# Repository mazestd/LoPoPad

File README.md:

# #️⃣ LoPoPad
4x3 Low Profile MacroPad with 1.9" LCD Display

# 💡Intro

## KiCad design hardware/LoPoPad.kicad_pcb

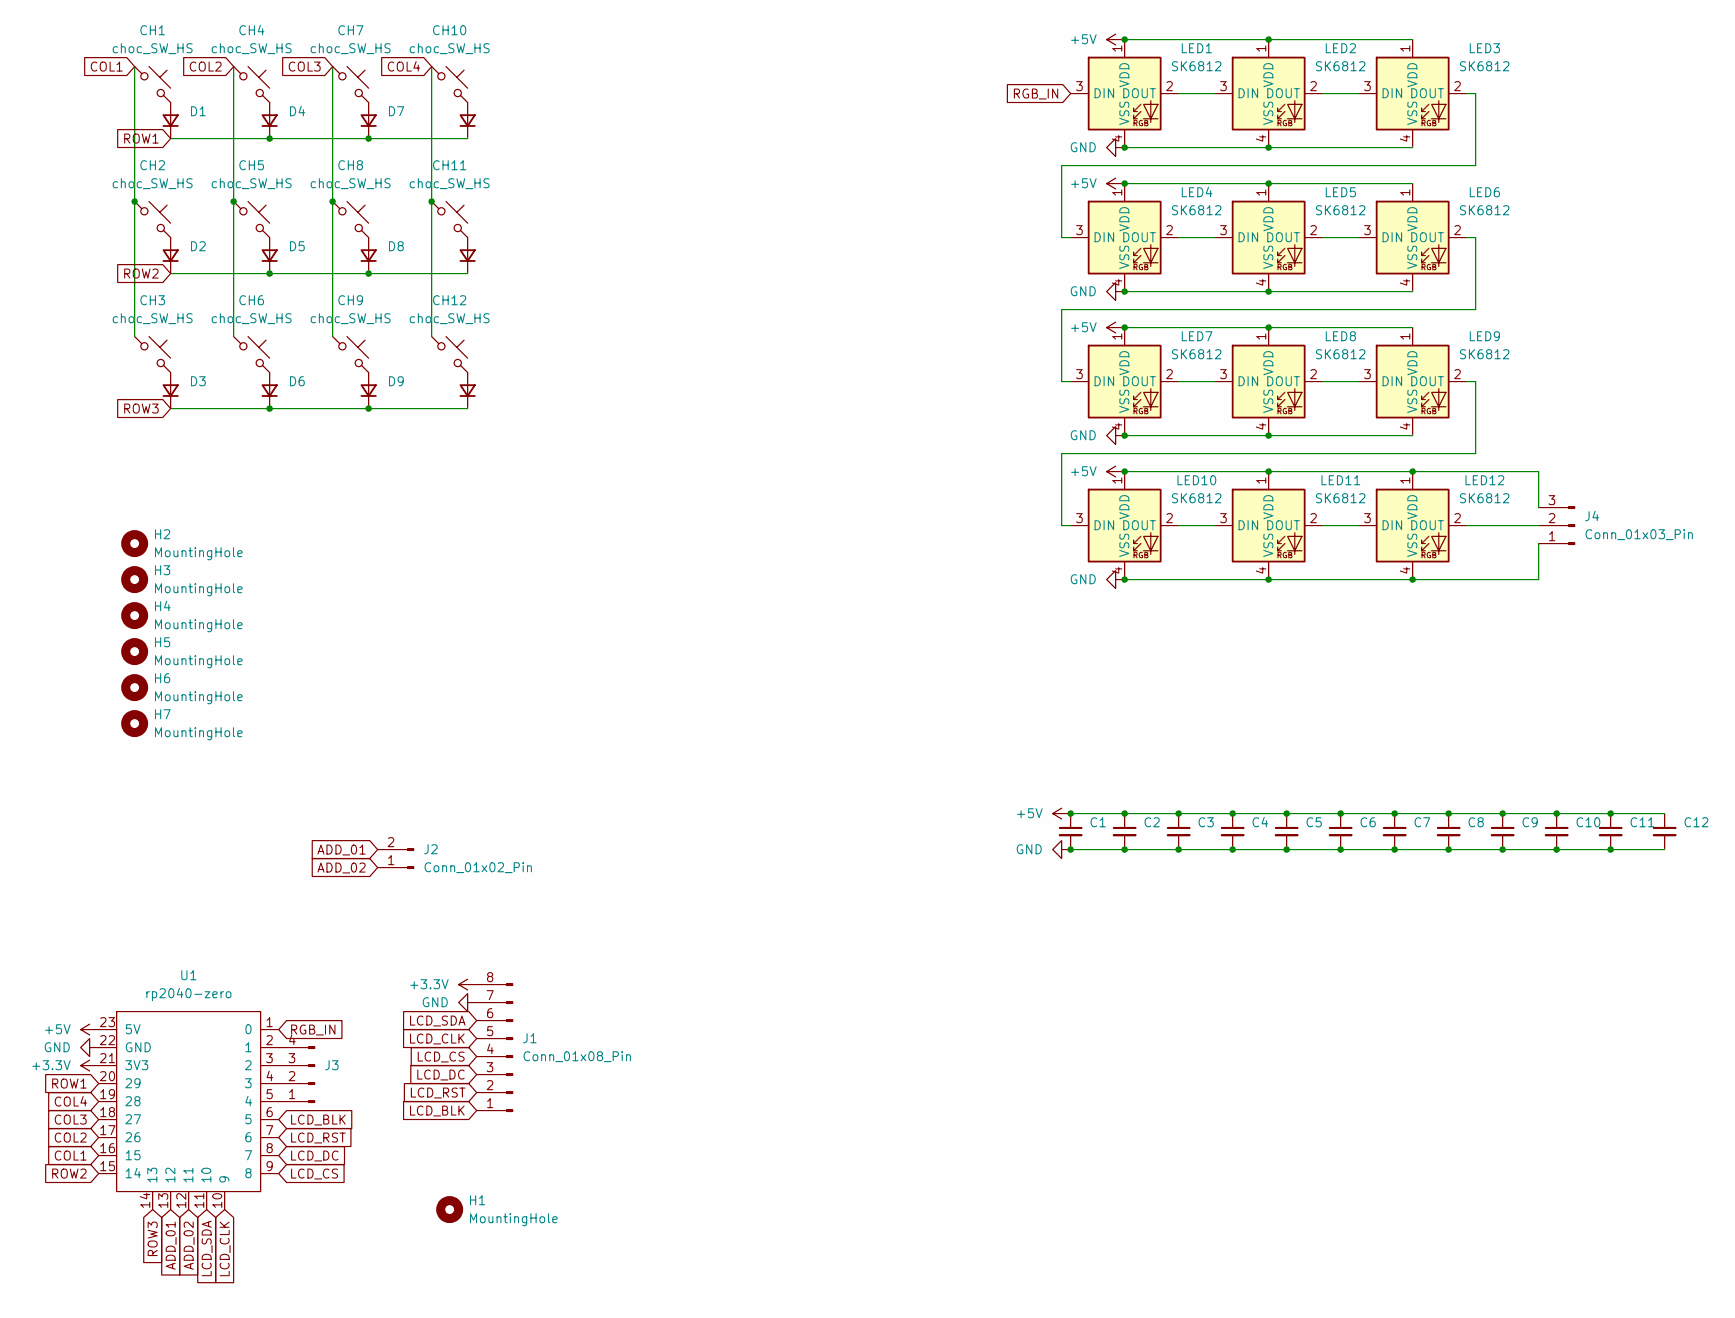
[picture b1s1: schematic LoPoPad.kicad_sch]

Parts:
C1, C2, C3, C4, C5, C6, C7, C8, C9, C10, C11, C12: 100nf; C_0603_1608Metric
CH1, CH2, CH3, CH4, CH5, CH6, CH7, CH8, CH9, CH10, CH11, CH12: choc_SW_HS; SW_choc_v1_HS_1u
D1, D2, D3, D4, D5, D6, D7, D8, D9, D10, D11, D12: 1n4148w; D_SOD-123
H1: MountingHole; soyu_display
H2, H3, H4, H5, H6, H7: MountingHole; MountingHole_2.2mm_M2_ISO14580
J1: Conn_01x08_Pin; Molex_PicoBlade_53261-0871_1x08-1MP_P1.25mm_Horizontal
J2: Conn_01x02_Pin; PinHeader_1x02_P2.54mm_Vertical
J3: Conn_01x04_Pin; PinHeader_1x04_P2.54mm_Vertical
J4: Conn_01x03_Pin; PinHeader_1x03_P2.00mm_Vertical
LED1, LED2, LED3, LED4, LED5, LED6, LED7, LED8, LED9, LED10, LED11, LED12: SK6812; LED_choc_6028R
U1: rp2040-zero; rp2040-zero-smd

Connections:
+3.3V: J1.8, U1.21 (3V3)
+5V: C1.1, C2.1, C3.1, C4.1, C5.1, C6.1, C7.1, C8.1, C9.1, C10.1, C11.1, C12.1, J4.3, LED1.1 (VDD), LED2.1 (VDD), LED3.1 (VDD), LED4.1 (VDD), LED5.1 (VDD), LED6.1 (VDD), LED7.1 (VDD), LED8.1 (VDD), LED9.1 (VDD), LED10.1 (VDD), LED11.1 (VDD), LED12.1 (VDD), U1.23 (5V)
ADD_01: J2.2, U1.13 (12)
ADD_02: J2.1, U1.12 (11)
COL1: CH1.1, CH2.1, CH3.1, U1.16 (15)
COL2: CH4.1, CH5.1, CH6.1, U1.17 (26)
COL3: CH7.1, CH8.1, CH9.1, U1.18 (27)
COL4: CH10.1, CH11.1, CH12.1, U1.19 (28)
GND: C1.2, C2.2, C3.2, C4.2, C5.2, C6.2, C7.2, C8.2, C9.2, C10.2, C11.2, C12.2, J1.7, J4.1, LED1.4 (VSS), LED2.4 (VSS), LED3.4 (VSS), LED4.4 (VSS), LED5.4 (VSS), LED6.4 (VSS), LED7.4 (VSS), LED8.4 (VSS), LED9.4 (VSS), LED10.4 (VSS), LED11.4 (VSS), LED12.4 (VSS), U1.22 (GND)
LCD_BLK: J1.1, U1.6 (5)
LCD_CLK: J1.5, U1.10 (9)
LCD_CS: J1.4, U1.9 (8)
LCD_DC: J1.3, U1.8 (7)
LCD_RST: J1.2, U1.7 (6)
LCD_SDA: J1.6, U1.11 (10)
unnamed: CH1.2, D1.2 (A)
unnamed: CH2.2, D2.2 (A)
unnamed: CH3.2, D3.2 (A)
unnamed: CH4.2, D4.2 (A)
unnamed: CH5.2, D5.2 (A)
unnamed: CH6.2, D6.2 (A)
unnamed: CH7.2, D7.2 (A)
unnamed: CH8.2, D8.2 (A)
unnamed: CH9.2, D9.2 (A)
unnamed: CH10.2, D10.2 (A)
unnamed: CH11.2, D11.2 (A)
unnamed: CH12.2, D12.2 (A)
unnamed: J3.1, U1.5 (4)
unnamed: J3.2, U1.4 (3)
unnamed: J3.3, U1.3 (2)
unnamed: J3.4, U1.2 (1)
unnamed: J4.2, LED12.2 (DOUT)
unnamed: LED1.2 (DOUT), LED2.3 (DIN)
unnamed: LED2.2 (DOUT), LED3.3 (DIN)
unnamed: LED3.2 (DOUT), LED4.3 (DIN)
unnamed: LED4.2 (DOUT), LED5.3 (DIN)
unnamed: LED5.2 (DOUT), LED6.3 (DIN)
unnamed: LED6.2 (DOUT), LED7.3 (DIN)
unnamed: LED7.2 (DOUT), LED8.3 (DIN)
unnamed: LED8.2 (DOUT), LED9.3 (DIN)
unnamed: LED9.2 (DOUT), LED10.3 (DIN)
unnamed: LED10.2 (DOUT), LED11.3 (DIN)
unnamed: LED11.2 (DOUT), LED12.3 (DIN)
RGB_IN: LED1.3 (DIN), U1.1 (0)
ROW1: D1.1 (K), D4.1 (K), D7.1 (K), D10.1 (K), U1.20 (29)
ROW2: D2.1 (K), D5.1 (K), D8.1 (K), D11.1 (K), U1.15 (14)
ROW3: D3.1 (K), D6.1 (K), D9.1 (K), D12.1 (K), U1.14 (13)

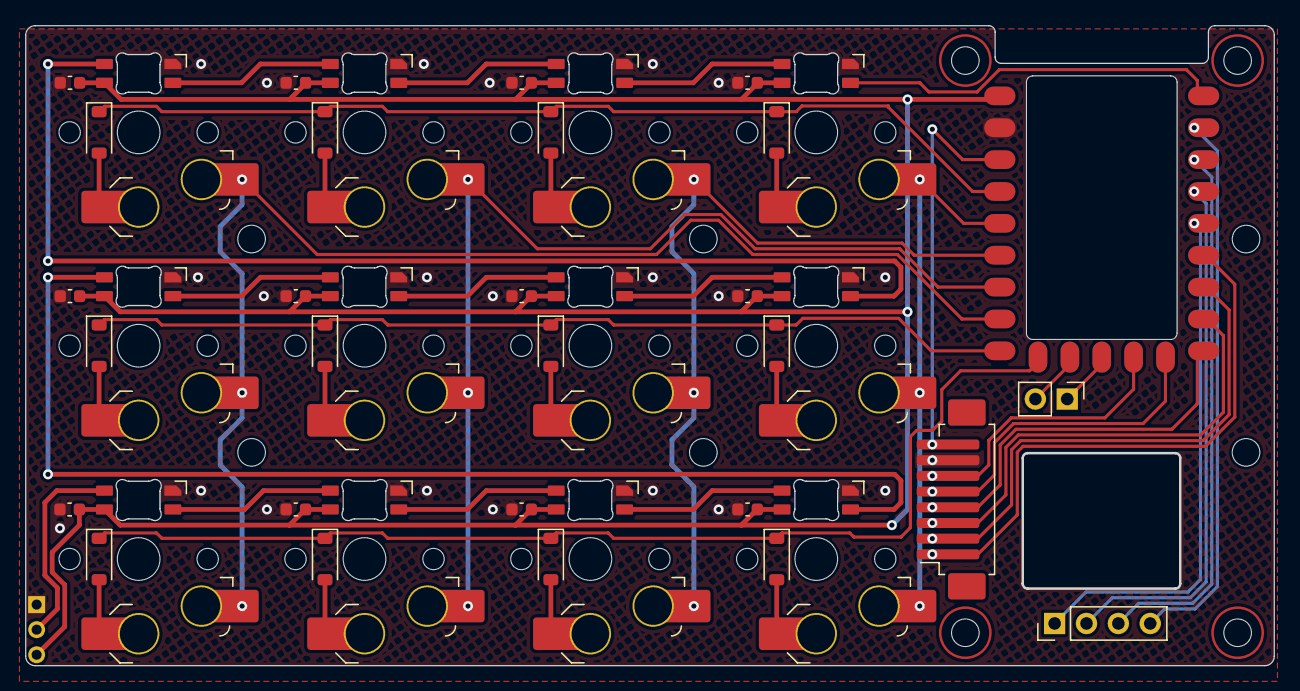
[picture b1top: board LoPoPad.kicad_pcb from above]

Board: 2 copper layers, 99.5 x 51.0 mm, 60 parts (1 on the bottom side), 47 nets.

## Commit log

2023-11-26 Initial release
2023-11-26 introduction #1
